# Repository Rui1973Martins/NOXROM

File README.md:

# NOXROM
 is a ZX Spectrum Cartridge compatible system, that extends the ROM size beyond 16KB

To use a NOXROM cartridge a regular cartridge interface is required to plug it in to a ZX Spectrum 48KB.

Common retro interfaces are:
- Sinclair ZX Interface 2
- RAM Turbo
- Kempston Pro

Modern tnterfaces also exist, with the same compatible Cartridge socket, like the "SPECTRA Interface" by Paul Farrows.

This is a hardware implementation of a new smart cartridge, that supports 128KB, 256KB or 512KB in Flash ROM, pageable in 16KB blocks. This is implemented using a CPLD (for control logic) and a parallel interface Flash chip from ATMEL.

NOXROM cartridge is smart, in the sense that it supports side band signaling, as a form of communication, that allows ZX software to control the internal cartridge paging register, hence allowing the use of the entire Flash chip memory, mapped into the ZX Spectrum ROM 16KB address space.

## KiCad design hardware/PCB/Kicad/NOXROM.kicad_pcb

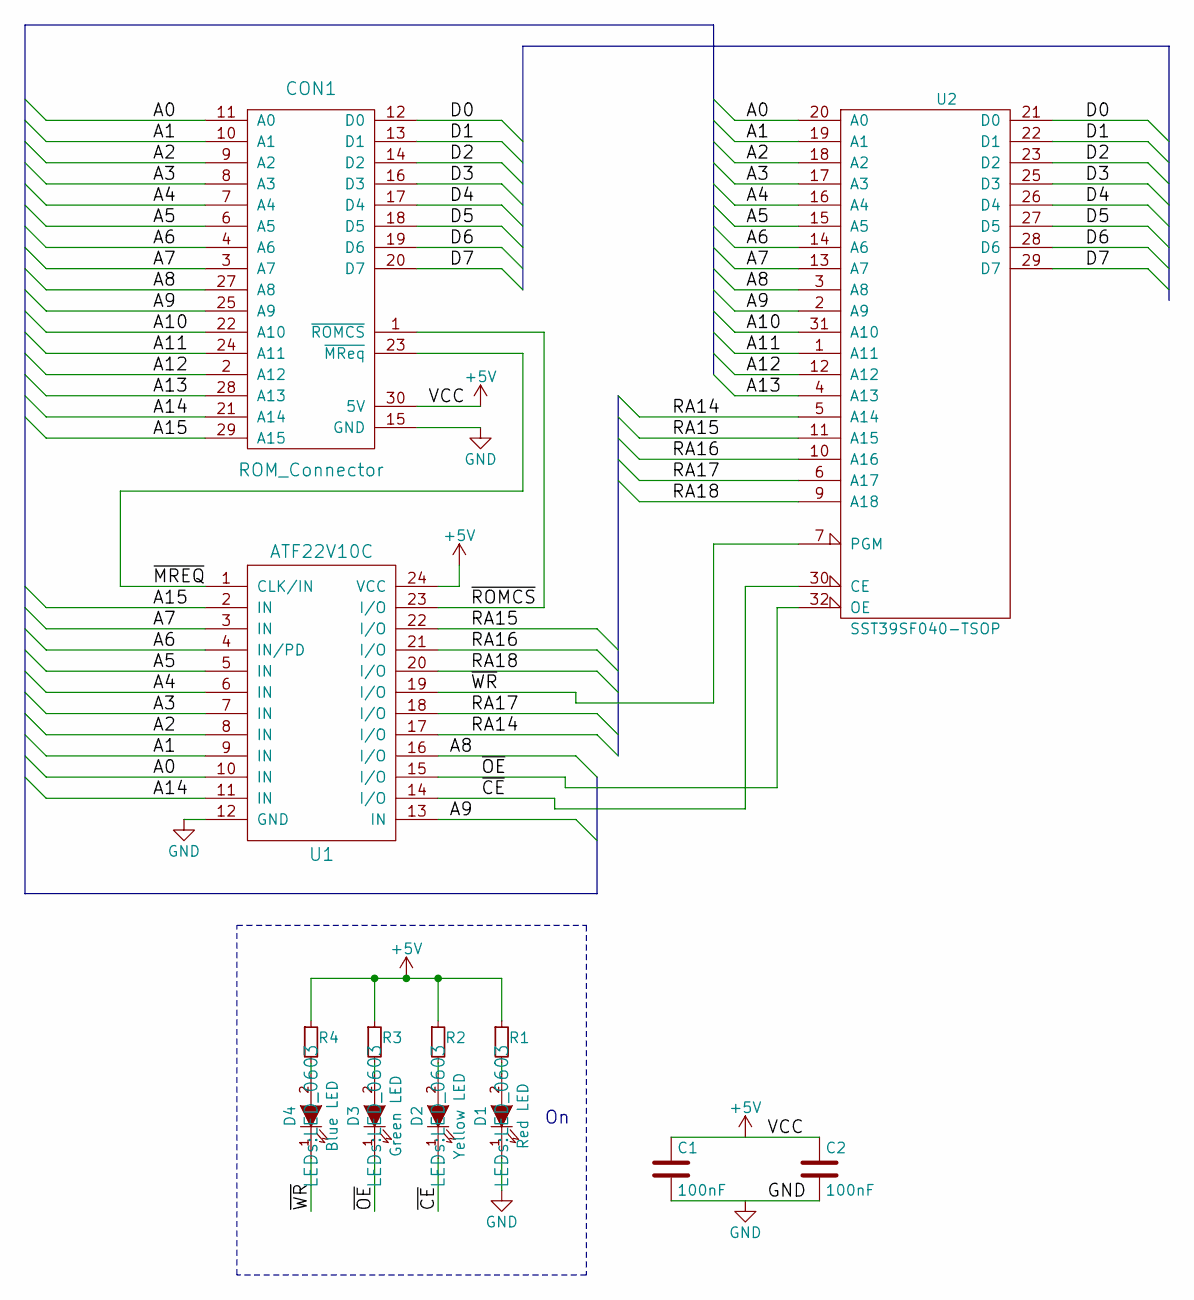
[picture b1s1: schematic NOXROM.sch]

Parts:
C1, C2: 100nF; C_0603
CON1: ROM_Connector; ZX_IF2_ROM_Edge_Connector
D1: Red LED; LED_0603
D2: Yellow LED; LED_0603
D3: Green LED; LED_0603
D4: Blue LED; LED_0603
R1, R2, R3, R4: R_Small; R_0603
U1: ATF22V10C; TSSOP-24_4.4x7.8mm_Pitch0.65mm
U2: SST39SF040-TSOP

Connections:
+5V: C1.1, C2.1, CON1.30 (5V), R1.1, R2.1, R3.1, R4.1, U1.24 (VCC), U2.8 (VCC)
/A0: CON1.11 (A0), U1.10 (IN), U2.20 (A0)
/A1: CON1.10 (A1), U1.9 (IN), U2.19 (A1)
/A2: CON1.9 (A2), U1.8 (IN), U2.18 (A2)
/A3: CON1.8 (A3), U1.7 (IN), U2.17 (A3)
/A4: CON1.7 (A4), U1.6 (IN), U2.16 (A4)
/A5: CON1.6 (A5), U1.5 (IN), U2.15 (A5)
/A6: CON1.4 (A6), U1.4 (IN/PD), U2.14 (A6)
/A7: CON1.3 (A7), U1.3 (IN), U2.13 (A7)
/A8: CON1.27 (A8), U1.16 (I/O), U2.3 (A8)
/A9: CON1.25 (A9), U1.13 (IN), U2.2 (A9)
/A10: CON1.22 (A10), U2.31 (A10)
/A11: CON1.24 (A11), U2.1 (A11)
/A12: CON1.2 (A12), U2.12 (A12)
/A13: CON1.28 (A13), U2.4 (A13)
/A14: CON1.21 (A14), U1.11 (IN)
/A15: CON1.29 (A15), U1.2 (IN)
/D0: CON1.12 (D0), U2.21 (D0)
/D1: CON1.13 (D1), U2.22 (D1)
/D2: CON1.14 (D2), U2.23 (D2)
/D3: CON1.16 (D3), U2.25 (D3)
/D4: CON1.17 (D4), U2.26 (D4)
/D5: CON1.18 (D5), U2.27 (D5)
/D6: CON1.19 (D6), U2.28 (D6)
/D7: CON1.20 (D7), U2.29 (D7)
/RA14: U1.17 (I/O), U2.5 (A14)
/RA15: U1.22 (I/O), U2.11 (A15)
/RA16: U1.21 (I/O), U2.10 (A16)
/RA17: U1.18 (I/O), U2.6 (A17)
/RA18: U1.20 (I/O), U2.9 (A18)
/~CE: D2.1 (K), U1.14 (I/O), U2.30 (CE)
/~MREQ: CON1.23 (~MReq), U1.1 (CLK/IN)
/~OE: D3.1 (K), U1.15 (I/O), U2.32 (OE)
/~ROMCS: CON1.1 (~ROMCS), U1.23 (I/O)
/~WR: D4.1 (K), U1.19 (I/O), U2.7 (PGM)
GND: C1.2, C2.2, CON1.15 (GND), D1.1 (K), U1.12 (GND), U2.24 (GND)
unnamed: D1.2 (A), R1.2
unnamed: D2.2 (A), R2.2
unnamed: D3.2 (A), R3.2
unnamed: D4.2 (A), R4.2

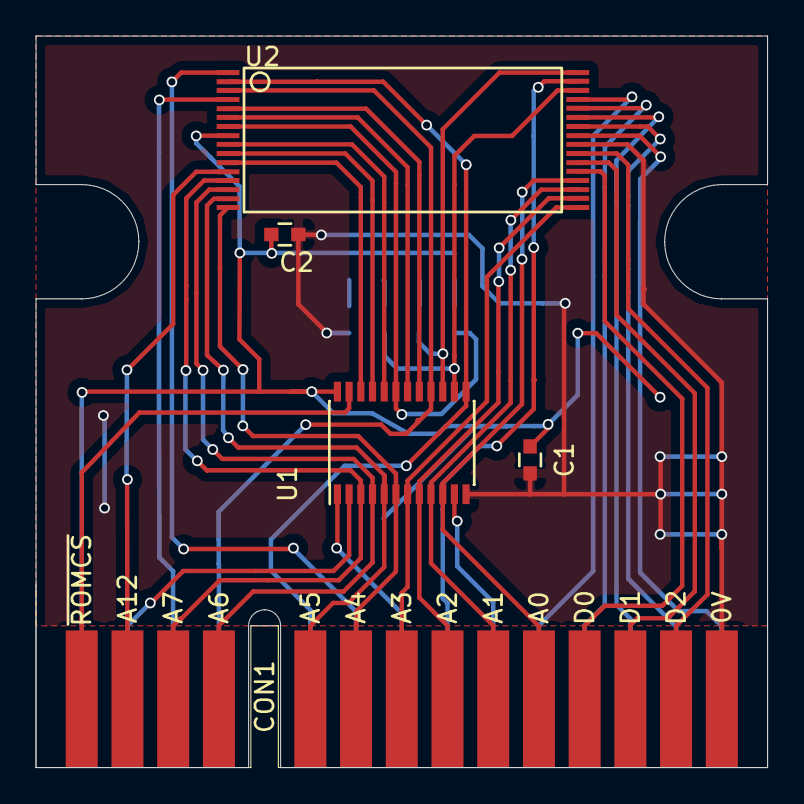
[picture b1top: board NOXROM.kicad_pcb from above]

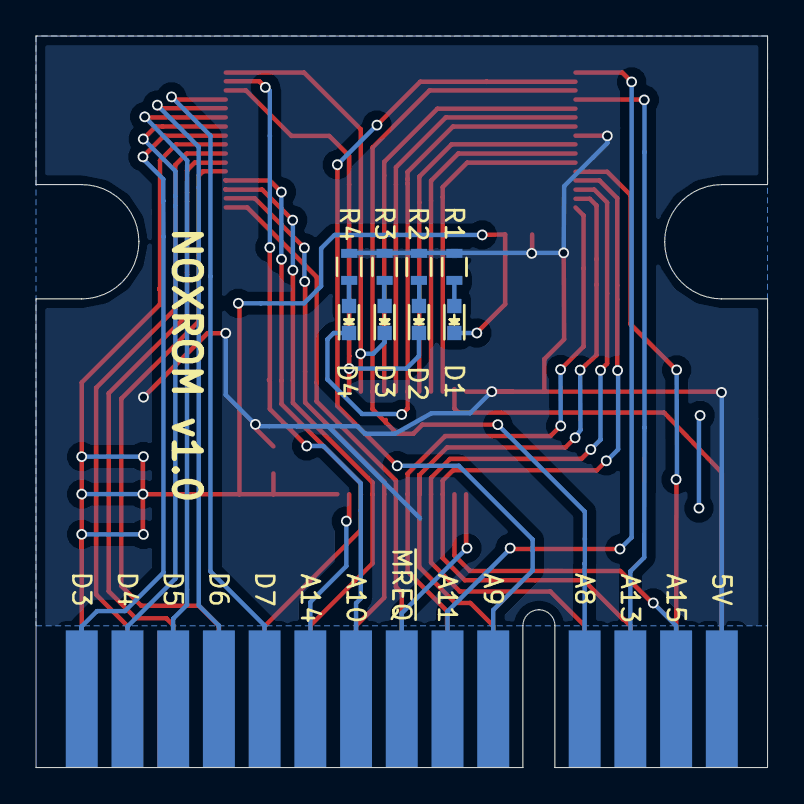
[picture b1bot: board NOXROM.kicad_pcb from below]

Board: 2 copper layers, 40.6 x 40.6 mm, 13 parts (8 on the bottom side), 40 nets.

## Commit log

2017-12-21 Version 1.0
2017-12-22 Update CPLD README file
2017-12-22 Add test firmware
2017-12-22 Update Firmware README
2017-12-22 Add TestFirmware sample screenshot
